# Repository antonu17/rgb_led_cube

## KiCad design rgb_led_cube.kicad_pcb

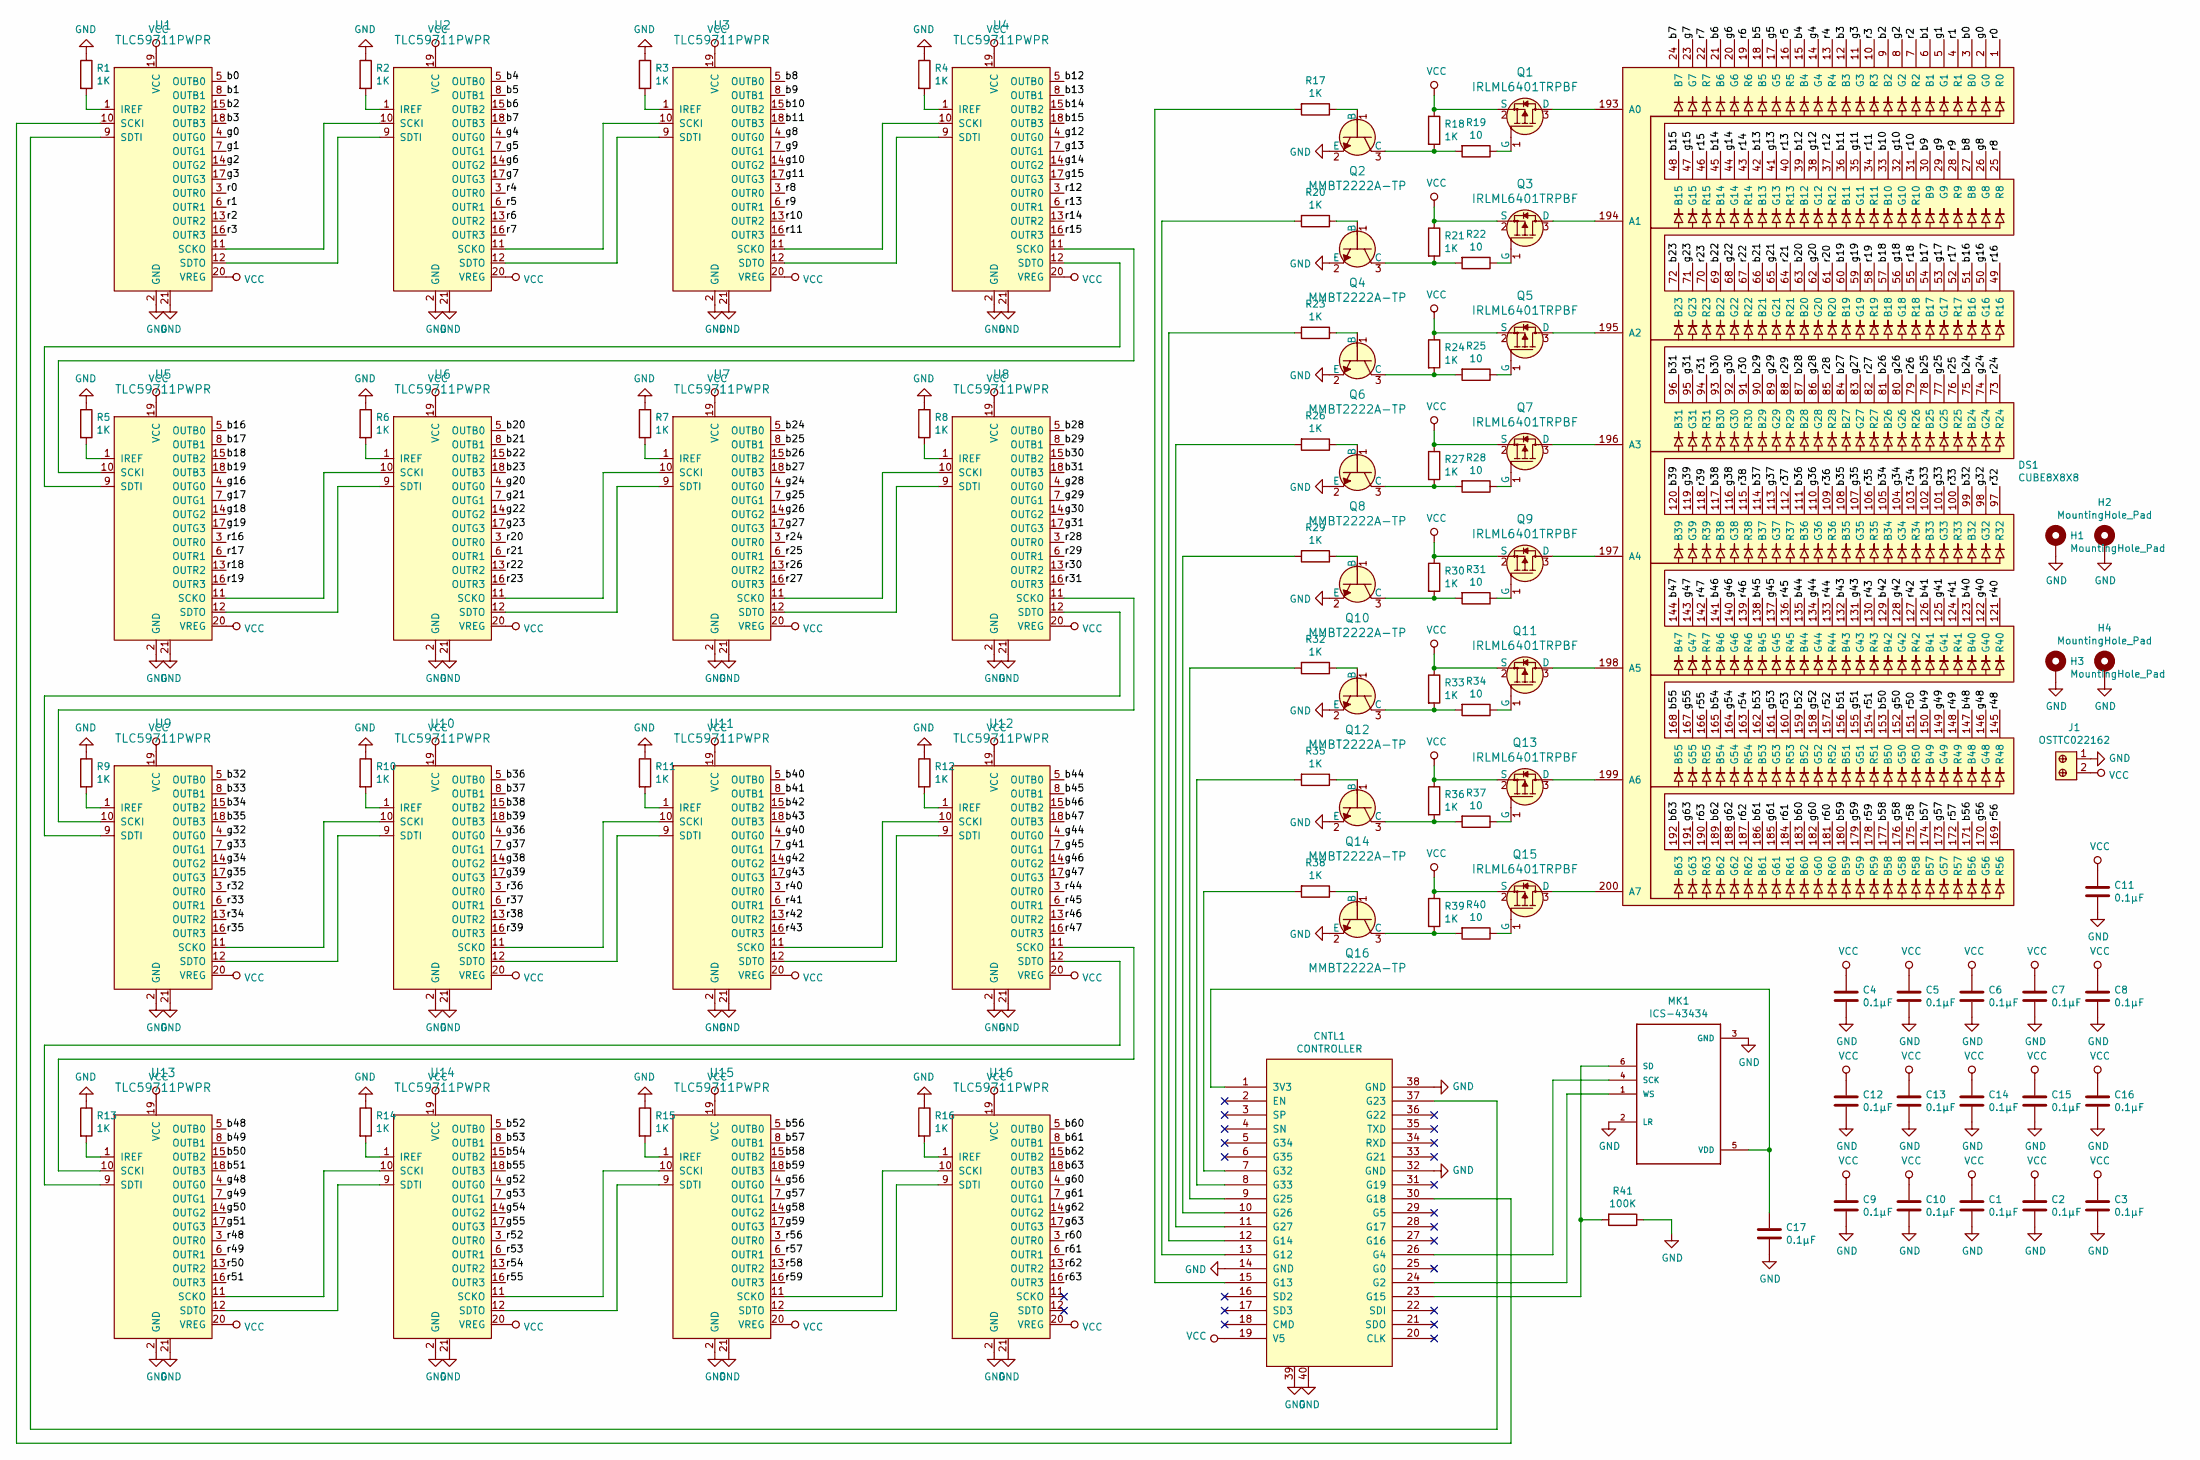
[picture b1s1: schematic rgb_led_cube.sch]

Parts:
C1, C2, C3, C4, C5, C6, C7, C8, C9, C10, C11, C12, C13, C14, C15, C16, C17: 0.1µF; C_0805_2012Metric_Pad1.15x1.40mm_HandSolder
CNTL1: CONTROLLER; ESP32_NodeMCU
DS1: CUBE8X8X8
H1, H2, H3, H4: MountingHole_Pad; MountingHole_3.2mm_M3_Pad_Via
J1: OSTTC022162; Term_Block_1x2_P5.08MM; MPN OSTTC022162; Digi-Key_PN ED2609-ND
MK1: ICS-43434; MIC_ICS-43434
Q1, Q3, Q5, Q7, Q9, Q11, Q13, Q15: IRLML6401TRPBF; SOT-23; MPN IRLML6401TRPBF; Digi-Key_PN IRLML6401PBFCT-ND
Q2, Q4, Q6, Q8, Q10, Q12, Q14, Q16: MMBT2222A-TP; SOT-23; MPN MMBT2222A-TP; Digi-Key_PN MMBT2222ATPMSCT-ND
R1, R2, R3, R4, R5, R6, R7, R8, R9, R10, R11, R12, R13, R14, R15, R16, R17, R18, R20, R21, R23, R24, R26, R27, R29, R30, R32, R33, R35, R36, R38, R39: 1K; R_0805_2012Metric_Pad1.15x1.40mm_HandSolder
R19, R22, R25, R28, R31, R34, R37, R40: 10; R_0805_2012Metric_Pad1.15x1.40mm_HandSolder
R41: 100K; R_0805_2012Metric_Pad1.15x1.40mm_HandSolder
U1, U2, U3, U4, U5, U6, U7, U8, U9, U10, U11, U12, U13, U14, U15, U16: TLC59711PWPR; HTSSOP-20-1EP_4.4x6.5mm_P0.65mm_EP3.4x6.5mm_Mask2.75x3.43mm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; MPN TLC59711PWPR; Digi-Key_PN 296-36745-1-ND

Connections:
/b0: DS1.3 (B0), U1.5 (OUTB0)
/b1: DS1.6 (B1), U1.8 (OUTB1)
/b2: DS1.9 (B2), U1.15 (OUTB2)
/b3: DS1.12 (B3), U1.18 (OUTB3)
/b4: DS1.15 (B4), U2.5 (OUTB0)
/b5: DS1.18 (B5), U2.8 (OUTB1)
/b6: DS1.21 (B6), U2.15 (OUTB2)
/b7: DS1.24 (B7), U2.18 (OUTB3)
/b8: DS1.27 (B8), U3.5 (OUTB0)
/b9: DS1.30 (B9), U3.8 (OUTB1)
/b10: DS1.33 (B10), U3.15 (OUTB2)
/b11: DS1.36 (B11), U3.18 (OUTB3)
/b12: DS1.39 (B12), U4.5 (OUTB0)
/b13: DS1.42 (B13), U4.8 (OUTB1)
/b14: DS1.45 (B14), U4.15 (OUTB2)
/b15: DS1.48 (B15), U4.18 (OUTB3)
/b16: DS1.51 (B16), U5.5 (OUTB0)
/b17: DS1.54 (B17), U5.8 (OUTB1)
/b18: DS1.57 (B18), U5.15 (OUTB2)
/b19: DS1.60 (B19), U5.18 (OUTB3)
/b20: DS1.63 (B20), U6.5 (OUTB0)
/b21: DS1.66 (B21), U6.8 (OUTB1)
/b22: DS1.69 (B22), U6.15 (OUTB2)
/b23: DS1.72 (B23), U6.18 (OUTB3)
/b24: DS1.75 (B24), U7.5 (OUTB0)
/b25: DS1.78 (B25), U7.8 (OUTB1)
/b26: DS1.81 (B26), U7.15 (OUTB2)
/b27: DS1.84 (B27), U7.18 (OUTB3)
/b28: DS1.87 (B28), U8.5 (OUTB0)
/b29: DS1.90 (B29), U8.8 (OUTB1)
/b30: DS1.93 (B30), U8.15 (OUTB2)
/b31: DS1.96 (B31), U8.18 (OUTB3)
/b32: DS1.99 (B32), U9.5 (OUTB0)
/b33: DS1.102 (B33), U9.8 (OUTB1)
/b34: DS1.105 (B34), U9.15 (OUTB2)
/b35: DS1.108 (B35), U9.18 (OUTB3)
/b36: DS1.111 (B36), U10.5 (OUTB0)
/b37: DS1.114 (B37), U10.8 (OUTB1)
/b38: DS1.117 (B38), U10.15 (OUTB2)
/b39: DS1.120 (B39), U10.18 (OUTB3)
/b40: DS1.123 (B40), U11.5 (OUTB0)
/b41: DS1.126 (B41), U11.8 (OUTB1)
/b42: DS1.129 (B42), U11.15 (OUTB2)
/b43: DS1.132 (B43), U11.18 (OUTB3)
/b44: DS1.135 (B44), U12.5 (OUTB0)
/b45: DS1.138 (B45), U12.8 (OUTB1)
/b46: DS1.141 (B46), U12.15 (OUTB2)
/b47: DS1.144 (B47), U12.18 (OUTB3)
/b48: DS1.147 (B48), U13.5 (OUTB0)
/b49: DS1.150 (B49), U13.8 (OUTB1)
/b50: DS1.153 (B50), U13.15 (OUTB2)
/b51: DS1.156 (B51), U13.18 (OUTB3)
/b52: DS1.159 (B52), U14.5 (OUTB0)
/b53: DS1.162 (B53), U14.8 (OUTB1)
/b54: DS1.165 (B54), U14.15 (OUTB2)
/b55: DS1.168 (B55), U14.18 (OUTB3)
/b56: DS1.171 (B56), U15.5 (OUTB0)
/b57: DS1.174 (B57), U15.8 (OUTB1)
/b58: DS1.177 (B58), U15.15 (OUTB2)
/b59: DS1.180 (B59), U15.18 (OUTB3)
/b60: DS1.183 (B60), U16.5 (OUTB0)
/b61: DS1.186 (B61), U16.8 (OUTB1)
/b62: DS1.189 (B62), U16.15 (OUTB2)
/b63: DS1.192 (B63), U16.18 (OUTB3)
/g0: DS1.2 (G0), U1.4 (OUTG0)
/g1: DS1.5 (G1), U1.7 (OUTG1)
/g2: DS1.8 (G2), U1.14 (OUTG2)
/g3: DS1.11 (G3), U1.17 (OUTG3)
/g4: DS1.14 (G4), U2.4 (OUTG0)
/g5: DS1.17 (G5), U2.7 (OUTG1)
/g6: DS1.20 (G6), U2.14 (OUTG2)
/g7: DS1.23 (G7), U2.17 (OUTG3)
/g8: DS1.26 (G8), U3.4 (OUTG0)
/g9: DS1.29 (G9), U3.7 (OUTG1)
/g10: DS1.32 (G10), U3.14 (OUTG2)
/g11: DS1.35 (G11), U3.17 (OUTG3)
/g12: DS1.38 (G12), U4.4 (OUTG0)
/g13: DS1.41 (G13), U4.7 (OUTG1)
/g14: DS1.44 (G14), U4.14 (OUTG2)
/g15: DS1.47 (G15), U4.17 (OUTG3)
/g16: DS1.50 (G16), U5.4 (OUTG0)
/g17: DS1.53 (G17), U5.7 (OUTG1)
/g18: DS1.56 (G18), U5.14 (OUTG2)
/g19: DS1.59 (G19), U5.17 (OUTG3)
/g20: DS1.62 (G20), U6.4 (OUTG0)
/g21: DS1.65 (G21), U6.7 (OUTG1)
/g22: DS1.68 (G22), U6.14 (OUTG2)
/g23: DS1.71 (G23), U6.17 (OUTG3)
/g24: DS1.74 (G24), U7.4 (OUTG0)
/g25: DS1.77 (G25), U7.7 (OUTG1)
/g26: DS1.80 (G26), U7.14 (OUTG2)
/g27: DS1.83 (G27), U7.17 (OUTG3)
/g28: DS1.86 (G28), U8.4 (OUTG0)
/g29: DS1.89 (G29), U8.7 (OUTG1)
/g30: DS1.92 (G30), U8.14 (OUTG2)
/g31: DS1.95 (G31), U8.17 (OUTG3)
/g32: DS1.98 (G32), U9.4 (OUTG0)
/g33: DS1.101 (G33), U9.7 (OUTG1)
/g34: DS1.104 (G34), U9.14 (OUTG2)
/g35: DS1.107 (G35), U9.17 (OUTG3)
/g36: DS1.110 (G36), U10.4 (OUTG0)
/g37: DS1.113 (G37), U10.7 (OUTG1)
/g38: DS1.116 (G38), U10.14 (OUTG2)
/g39: DS1.119 (G39), U10.17 (OUTG3)
/g40: DS1.122 (G40), U11.4 (OUTG0)
/g41: DS1.125 (G41), U11.7 (OUTG1)
/g42: DS1.128 (G42), U11.14 (OUTG2)
/g43: DS1.131 (G43), U11.17 (OUTG3)
/g44: DS1.134 (G44), U12.4 (OUTG0)
/g45: DS1.137 (G45), U12.7 (OUTG1)
/g46: DS1.140 (G46), U12.14 (OUTG2)
/g47: DS1.143 (G47), U12.17 (OUTG3)
/g48: DS1.146 (G48), U13.4 (OUTG0)
/g49: DS1.149 (G49), U13.7 (OUTG1)
/g50: DS1.152 (G50), U13.14 (OUTG2)
/g51: DS1.155 (G51), U13.17 (OUTG3)
/g52: DS1.158 (G52), U14.4 (OUTG0)
/g53: DS1.161 (G53), U14.7 (OUTG1)
/g54: DS1.164 (G54), U14.14 (OUTG2)
/g55: DS1.167 (G55), U14.17 (OUTG3)
/g56: DS1.170 (G56), U15.4 (OUTG0)
/g57: DS1.173 (G57), U15.7 (OUTG1)
/g58: DS1.176 (G58), U15.14 (OUTG2)
/g59: DS1.179 (G59), U15.17 (OUTG3)
/g60: DS1.182 (G60), U16.4 (OUTG0)
/g61: DS1.185 (G61), U16.7 (OUTG1)
/g62: DS1.188 (G62), U16.14 (OUTG2)
/g63: DS1.191 (G63), U16.17 (OUTG3)
/r0: DS1.1 (R0), U1.3 (OUTR0)
/r1: DS1.4 (R1), U1.6 (OUTR1)
/r2: DS1.7 (R2), U1.13 (OUTR2)
/r3: DS1.10 (R3), U1.16 (OUTR3)
/r4: DS1.13 (R4), U2.3 (OUTR0)
/r5: DS1.16 (R5), U2.6 (OUTR1)
/r6: DS1.19 (R6), U2.13 (OUTR2)
/r7: DS1.22 (R7), U2.16 (OUTR3)
/r8: DS1.25 (R8), U3.3 (OUTR0)
/r9: DS1.28 (R9), U3.6 (OUTR1)
/r10: DS1.31 (R10), U3.13 (OUTR2)
/r11: DS1.34 (R11), U3.16 (OUTR3)
/r12: DS1.37 (R12), U4.3 (OUTR0)
/r13: DS1.40 (R13), U4.6 (OUTR1)
/r14: DS1.43 (R14), U4.13 (OUTR2)
/r15: DS1.46 (R15), U4.16 (OUTR3)
/r16: DS1.49 (R16), U5.3 (OUTR0)
/r17: DS1.52 (R17), U5.6 (OUTR1)
/r18: DS1.55 (R18), U5.13 (OUTR2)
/r19: DS1.58 (R19), U5.16 (OUTR3)
/r20: DS1.61 (R20), U6.3 (OUTR0)
/r21: DS1.64 (R21), U6.6 (OUTR1)
/r22: DS1.67 (R22), U6.13 (OUTR2)
/r23: DS1.70 (R23), U6.16 (OUTR3)
/r24: DS1.73 (R24), U7.3 (OUTR0)
/r25: DS1.76 (R25), U7.6 (OUTR1)
/r26: DS1.79 (R26), U7.13 (OUTR2)
/r27: DS1.82 (R27), U7.16 (OUTR3)
/r28: DS1.85 (R28), U8.3 (OUTR0)
/r29: DS1.88 (R29), U8.6 (OUTR1)
/r30: DS1.91 (R30), U8.13 (OUTR2)
/r31: DS1.94 (R31), U8.16 (OUTR3)
/r32: DS1.97 (R32), U9.3 (OUTR0)
/r33: DS1.100 (R33), U9.6 (OUTR1)
/r34: DS1.103 (R34), U9.13 (OUTR2)
/r35: DS1.106 (R35), U9.16 (OUTR3)
/r36: DS1.109 (R36), U10.3 (OUTR0)
/r37: DS1.112 (R37), U10.6 (OUTR1)
/r38: DS1.115 (R38), U10.13 (OUTR2)
/r39: DS1.118 (R39), U10.16 (OUTR3)
/r40: DS1.121 (R40), U11.3 (OUTR0)
/r41: DS1.124 (R41), U11.6 (OUTR1)
/r42: DS1.127 (R42), U11.13 (OUTR2)
/r43: DS1.130 (R43), U11.16 (OUTR3)
/r44: DS1.133 (R44), U12.3 (OUTR0)
/r45: DS1.136 (R45), U12.6 (OUTR1)
/r46: DS1.139 (R46), U12.13 (OUTR2)
/r47: DS1.142 (R47), U12.16 (OUTR3)
/r48: DS1.145 (R48), U13.3 (OUTR0)
/r49: DS1.148 (R49), U13.6 (OUTR1)
/r50: DS1.151 (R50), U13.13 (OUTR2)
/r51: DS1.154 (R51), U13.16 (OUTR3)
/r52: DS1.157 (R52), U14.3 (OUTR0)
/r53: DS1.160 (R53), U14.6 (OUTR1)
/r54: DS1.163 (R54), U14.13 (OUTR2)
/r55: DS1.166 (R55), U14.16 (OUTR3)
/r56: DS1.169 (R56), U15.3 (OUTR0)
/r57: DS1.172 (R57), U15.6 (OUTR1)
/r58: DS1.175 (R58), U15.13 (OUTR2)
/r59: DS1.178 (R59), U15.16 (OUTR3)
/r60: DS1.181 (R60), U16.3 (OUTR0)
/r61: DS1.184 (R61), U16.6 (OUTR1)
/r62: DS1.187 (R62), U16.13 (OUTR2)
/r63: DS1.190 (R63), U16.16 (OUTR3)
GND: C1.2, C2.2, C3.2, C4.2, C5.2, C6.2, C7.2, C8.2, C9.2, C10.2, C11.2, C12.2, C13.2, C14.2, C15.2, C16.2, C17.2, CNTL1.14 (GND), CNTL1.32 (GND), CNTL1.38 (GND), CNTL1.39, CNTL1.40, H1.1, H2.1, H3.1, H4.1, J1.1, MK1.2 (LR), MK1.3 (GND), Q2.2 (E), Q4.2 (E), Q6.2 (E), Q8.2 (E), Q10.2 (E), Q12.2 (E), Q14.2 (E), Q16.2 (E), R1.1, R2.1, R3.1, R4.1, R5.1, R6.1, R7.1, R8.1, R9.1, R10.1, R11.1, R12.1, R13.1, R14.1, R15.1, R16.1, R41.1, U1.2 (GND), U1.21, U2.2 (GND), U2.21, U3.2 (GND), U3.21, U4.2 (GND), U4.21, U5.2 (GND), U5.21, U6.2 (GND), U6.21, U7.2 (GND), U7.21, U8.2 (GND), U8.21, U9.2 (GND), U9.21, U10.2 (GND), U10.21, U11.2 (GND), U11.21, U12.2 (GND), U12.21, U13.2 (GND), U13.21, U14.2 (GND), U14.21, U15.2 (GND), U15.21, U16.2 (GND), U16.21
unnamed: C17.1, CNTL1.1 (3V3), MK1.5 (VDD)
unnamed: CNTL1.7 (G32), R38.2
unnamed: CNTL1.8 (G33), R35.2
unnamed: CNTL1.9 (G25), R32.2
unnamed: CNTL1.10 (G26), R29.2
unnamed: CNTL1.11 (G27), R26.2
unnamed: CNTL1.12 (G14), R23.2
unnamed: CNTL1.13 (G12), R20.2
unnamed: CNTL1.15 (G13), R17.2
unnamed: CNTL1.23 (G15), MK1.6 (SD), R41.2
unnamed: CNTL1.24 (G2), MK1.1 (WS)
unnamed: CNTL1.26 (G4), MK1.4 (SCK)
unnamed: CNTL1.30 (G18), U1.10 (SCKI)
unnamed: CNTL1.37 (G23), U1.9 (SDTI)
unnamed: DS1.193 (A0), Q1.3 (D)
unnamed: DS1.194 (A1), Q3.3 (D)
unnamed: DS1.195 (A2), Q5.3 (D)
unnamed: DS1.196 (A3), Q7.3 (D)
unnamed: DS1.197 (A4), Q9.3 (D)
unnamed: DS1.198 (A5), Q11.3 (D)
unnamed: DS1.199 (A6), Q13.3 (D)
unnamed: DS1.200 (A7), Q15.3 (D)
unnamed: Q1.1 (G), R19.1
unnamed: Q2.1 (B), R17.1
unnamed: Q2.3 (C), R18.2, R19.2
unnamed: Q3.1 (G), R22.1
unnamed: Q4.1 (B), R20.1
unnamed: Q4.3 (C), R21.2, R22.2
unnamed: Q5.1 (G), R25.1
unnamed: Q6.1 (B), R23.1
unnamed: Q6.3 (C), R24.2, R25.2
unnamed: Q7.1 (G), R28.1
unnamed: Q8.1 (B), R26.1
unnamed: Q8.3 (C), R27.2, R28.2
unnamed: Q9.1 (G), R31.1
unnamed: Q10.1 (B), R29.1
unnamed: Q10.3 (C), R30.2, R31.2
unnamed: Q11.1 (G), R34.1
unnamed: Q12.1 (B), R32.1
unnamed: Q12.3 (C), R33.2, R34.2
unnamed: Q13.1 (G), R37.1
unnamed: Q14.1 (B), R35.1
unnamed: Q14.3 (C), R36.2, R37.2
unnamed: Q15.1 (G), R40.1
unnamed: Q16.1 (B), R38.1
unnamed: Q16.3 (C), R39.2, R40.2
unnamed: R1.2, U1.1 (IREF)
unnamed: R2.2, U2.1 (IREF)
unnamed: R3.2, U3.1 (IREF)
unnamed: R4.2, U4.1 (IREF)
unnamed: R5.2, U5.1 (IREF)
unnamed: R6.2, U6.1 (IREF)
unnamed: R7.2, U7.1 (IREF)
unnamed: R8.2, U8.1 (IREF)
unnamed: R9.2, U9.1 (IREF)
unnamed: R10.2, U10.1 (IREF)
unnamed: R11.2, U11.1 (IREF)
unnamed: R12.2, U12.1 (IREF)
unnamed: R13.2, U13.1 (IREF)
unnamed: R14.2, U14.1 (IREF)
unnamed: R15.2, U15.1 (IREF)
unnamed: R16.2, U16.1 (IREF)
unnamed: U1.11 (SCKO), U2.10 (SCKI)
unnamed: U1.12 (SDTO), U2.9 (SDTI)
unnamed: U2.11 (SCKO), U3.10 (SCKI)
unnamed: U2.12 (SDTO), U3.9 (SDTI)
unnamed: U3.11 (SCKO), U4.10 (SCKI)
unnamed: U3.12 (SDTO), U4.9 (SDTI)
unnamed: U4.11 (SCKO), U5.10 (SCKI)
unnamed: U4.12 (SDTO), U5.9 (SDTI)
unnamed: U5.11 (SCKO), U6.10 (SCKI)
unnamed: U5.12 (SDTO), U6.9 (SDTI)
unnamed: U6.11 (SCKO), U7.10 (SCKI)
unnamed: U6.12 (SDTO), U7.9 (SDTI)
unnamed: U7.11 (SCKO), U8.10 (SCKI)
unnamed: U7.12 (SDTO), U8.9 (SDTI)
unnamed: U8.11 (SCKO), U9.10 (SCKI)
unnamed: U8.12 (SDTO), U9.9 (SDTI)
unnamed: U9.12 (SDTO), U10.9 (SDTI)
unnamed: U9.11 (SCKO), U10.10 (SCKI)
unnamed: U10.11 (SCKO), U11.10 (SCKI)
unnamed: U10.12 (SDTO), U11.9 (SDTI)
unnamed: U11.11 (SCKO), U12.10 (SCKI)
unnamed: U11.12 (SDTO), U12.9 (SDTI)
unnamed: U12.11 (SCKO), U13.10 (SCKI)
unnamed: U12.12 (SDTO), U13.9 (SDTI)
unnamed: U13.11 (SCKO), U14.10 (SCKI)
unnamed: U13.12 (SDTO), U14.9 (SDTI)
unnamed: U14.11 (SCKO), U15.10 (SCKI)
unnamed: U14.12 (SDTO), U15.9 (SDTI)
unnamed: U15.11 (SCKO), U16.10 (SCKI)
unnamed: U15.12 (SDTO), U16.9 (SDTI)
VCC: C1.1, C2.1, C3.1, C4.1, C5.1, C6.1, C7.1, C8.1, C9.1, C10.1, C11.1, C12.1, C13.1, C14.1, C15.1, C16.1, CNTL1.19 (V5), J1.2, Q1.2 (S), Q3.2 (S), Q5.2 (S), Q7.2 (S), Q9.2 (S), Q11.2 (S), Q13.2 (S), Q15.2 (S), R18.1, R21.1, R24.1, R27.1, R30.1, R33.1, R36.1, R39.1, U1.19 (VCC), U1.20 (VREG), U2.19 (VCC), U2.20 (VREG), U3.19 (VCC), U3.20 (VREG), U4.19 (VCC), U4.20 (VREG), U5.19 (VCC), U5.20 (VREG), U6.19 (VCC), U6.20 (VREG), U7.19 (VCC), U7.20 (VREG), U8.19 (VCC), U8.20 (VREG), U9.19 (VCC), U9.20 (VREG), U10.19 (VCC), U10.20 (VREG), U11.19 (VCC), U11.20 (VREG), U12.19 (VCC), U12.20 (VREG), U13.19 (VCC), U13.20 (VREG), U14.19 (VCC), U14.20 (VREG), U15.19 (VCC), U15.20 (VREG), U16.19 (VCC), U16.20 (VREG)

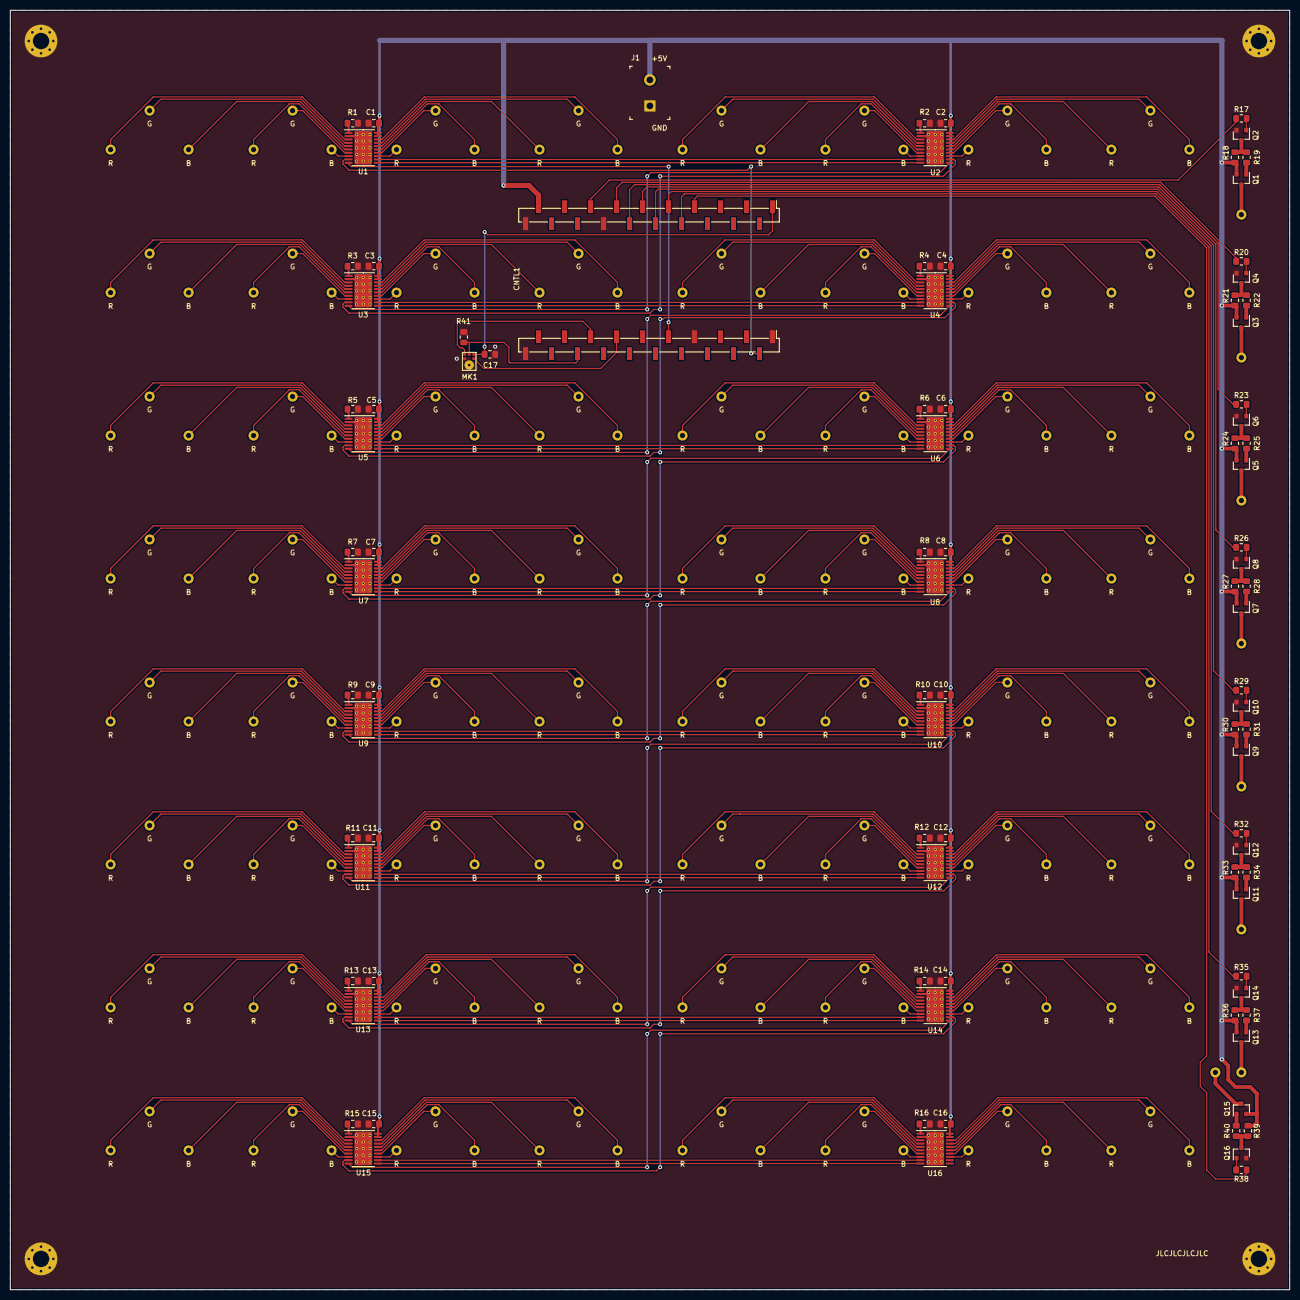
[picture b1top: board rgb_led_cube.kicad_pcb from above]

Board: 2 copper layers, 250.0 x 250.0 mm, 98 parts (1 on the bottom side), 286 nets.

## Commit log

2020-04-23 Add kicad project
2020-04-23 Arrange TLC with resistors and capacitors
2020-04-25 Update components placement
2020-04-25 Route ICs
2020-04-30 Update esp32 3d model
2020-05-02 Route pcb
2020-05-02 Connect unused header pins to GND
2020-05-02 Update netlist
2020-05-02 Increase VCC tracks width
2020-05-02 Update controller 3d model
2020-05-10 Update local footprints
2020-05-10 Add microphone
2020-05-10 Improve wiring
2020-05-17 Update layout
2020-05-19 PCB v2
2020-05-19 Remove model
2020-05-19 Align tracks
2021-01-18 Add Mounting holes
2021-01-18 Add ltspice simulation for mosfet
2021-01-18 Add gerbers
